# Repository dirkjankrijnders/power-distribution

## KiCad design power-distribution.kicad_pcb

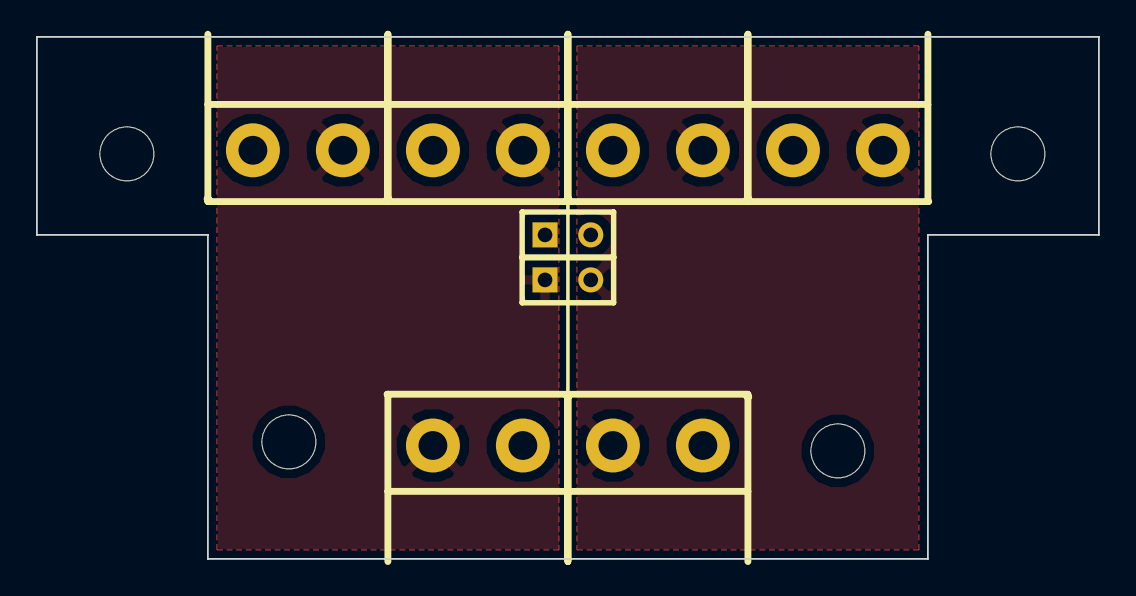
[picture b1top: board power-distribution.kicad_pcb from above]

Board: 2 copper layers, 59.0 x 29.0 mm, 12 parts (0 on the bottom side), 4 nets, no tracks yet.

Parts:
CON1, CON2, CON3, CON4, CON5, CON6: 2PIN_SCREWTERMINAL; 2PIN_Screw_Block
JP1, JP2: JUMPER; SIL-2
M1, M2, M3, M4: Mounting_hole; MountingHole_3mm

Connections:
unnamed: CON1.1, CON2.1, CON5.1, JP1.1
unnamed: CON1.2, CON2.2, CON5.2, JP2.1
unnamed: CON3.1, CON4.1, CON6.1, JP1.2
unnamed: CON3.2, CON4.2, CON6.2, JP2.2

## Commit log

2014-09-11 Created empty project
2014-09-11 Added first schematic and netlist
2014-09-15 Added mounting holes and two more connectors
2014-09-15 Split into two power planes, with jumpers in the middle to connect
2014-09-15 Made the board, rev.0
